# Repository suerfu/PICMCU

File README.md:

# PIC16F1788
Compilation of various code used to program PIC16F1788

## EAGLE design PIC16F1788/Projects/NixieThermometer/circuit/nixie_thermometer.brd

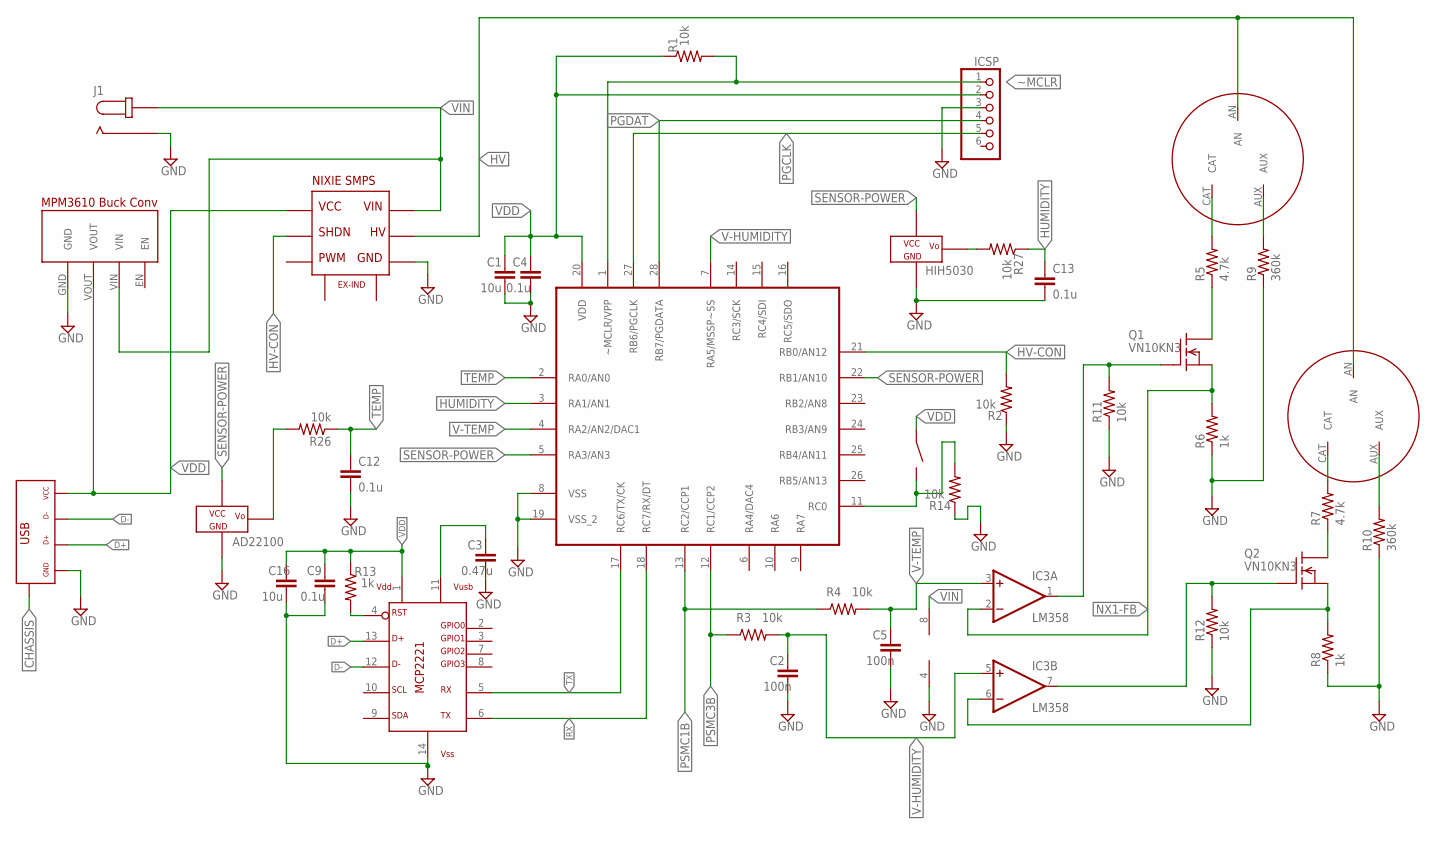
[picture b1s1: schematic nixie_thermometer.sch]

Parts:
AD22100: AD22100; TO-92
C1, C16: 10u; C0805
C2, C5: 100n; C0805
C3: 0.47u; C0805
C4, C9: 0.1u; C0805
C12, C13: 0.1u; C1206
HIH5030: HIH5030
IC1: PIC16F1788; DIP-28
IC2: MCP2221; SOIC-14
IC3: LM358; DIP-8
ICSP: PINHD-1X6; 1X06
J1: CONN-DC-JACK-PANEL; DC-JACK
Q1, Q2: VN10KN3; TO-92
R1, R2, R3, R4, R14, R26, R27: 10k; R0805
R5, R7: 4.7k; R0204/7
R6, R8: 1k; R0204/7
R9, R10: 360k; R0204/7
R11, R12: 10k; R0204/7
R13: 1k; R0805
U$1: MPM3610-ADAFRUIT; MPM3610-ADAFRUIT-MODULE
U$2: SMPS-HV-MODULE; SMPS-HV-MOD-MODULE
U$3, U$4: IN-13
U$5: SW-SPST-PUSHBUTTONSMD; SW-SPST-PUSHBUTTON-UNKNOWN-SMD
USB$2: USB-MILLMAX-896-43-004; USB-MILLMAX-896-43-004-90

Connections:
CHASSIS: USB$2.P$5 (SHIELD), USB$2.P$6 (SHIELD)
D+: IC2.13 (DP), USB$2.D+
D-: IC2.12 (DM), USB$2.D-
GND: AD22100.3 (GND), C1.2, C2.2, C3.2, C4.2, C5.2, C9.2, C12.2, C13.2, C16.2, HIH5030.GND, IC1.8 (VSS), IC1.19 (VSS_2), IC2.14 (VSS), IC3.4 (V-), ICSP.3, J1.GND-BOT (GND), J1.GND-TOP (GND), R2.1, R6.1, R8.1, R9.1, R10.1, R11.1, R12.1, R14.1, U$1.GND, U$2.GND, U$2.GND-HV (GND), USB$2.GND
HUMID-RAW: HIH5030.VO, R27.2
HUMIDITY: C13.1, IC1.3 (RA1/AN1), R27.1
HV: U$2.HV, U$3.AN, U$4.AN
HV-CON: IC1.21 (RB0/AN12), R2.2, U$2.SHDN
unnamed: IC1.11 (RC0), R14.2, U$5.P$6, U$5.P$8
unnamed: Q1.3 (D), R5.1
unnamed: Q2.3 (D), R7.1
unnamed: C3.1, IC2.11 (VUSB)
unnamed: R9.2, U$3.AUX
unnamed: R10.2, U$4.AUX
unnamed: R5.2, U$3.CAT
unnamed: R7.2, U$4.CAT
unnamed: IC2.4 (RST), R13.2
NX1-DRIVE: IC3.1 (OUT), Q1.2 (G), R11.2
NX1-FB: IC3.2 (-IN), Q1.1 (S), R6.2
NX2-DRIVE: IC3.7 (OUT), Q2.2 (G), R12.2
NX2-FB: IC3.6 (-IN), Q2.1 (S), R8.2
PGCLK: IC1.27 (RB6/PGCLK), ICSP.5
PGDAT: IC1.28 (RB7/PGDATA), ICSP.4
PSMC1B: IC1.13 (RC2/CCP1), R4.1
PSMC3B: IC1.12 (RC1/CCP2), R3.1
RX: IC1.18 (RC7/RX/DT), IC2.6 (TX)
SENSOR-POWER: AD22100.1 (VCC), HIH5030.VCC, IC1.5 (RA3/AN3), IC1.22 (RB1/AN10)
TEMP: C12.1, IC1.2 (RA0/AN0), R26.1
TEMP-RAW: AD22100.2 (VO), R26.2
TX: IC1.17 (RC6/TX/CK), IC2.5 (RX)
V-HUMIDITY: C2.1, IC1.7 (RA5/MSSP~SS), IC3.5 (+IN), R3.2
V-TEMP: C5.1, IC1.4 (RA2/AN2/DAC1), IC3.3 (+IN), R4.2
VDD: C1.1, C4.1, C9.1, C16.1, IC1.20 (VDD), IC2.1 (VDD), ICSP.2, R1.1, R13.1, U$1.VOUT, U$2.VDD (VCC), U$5.P$5, U$5.P$7, USB$2.VCC
VIN: IC3.8 (V+), J1.POW-BOT (POW), J1.POW-TOP (POW), U$1.VIN, U$2.VIN
~MCLR: IC1.1 (~MCLR/VPP), ICSP.1, R1.2

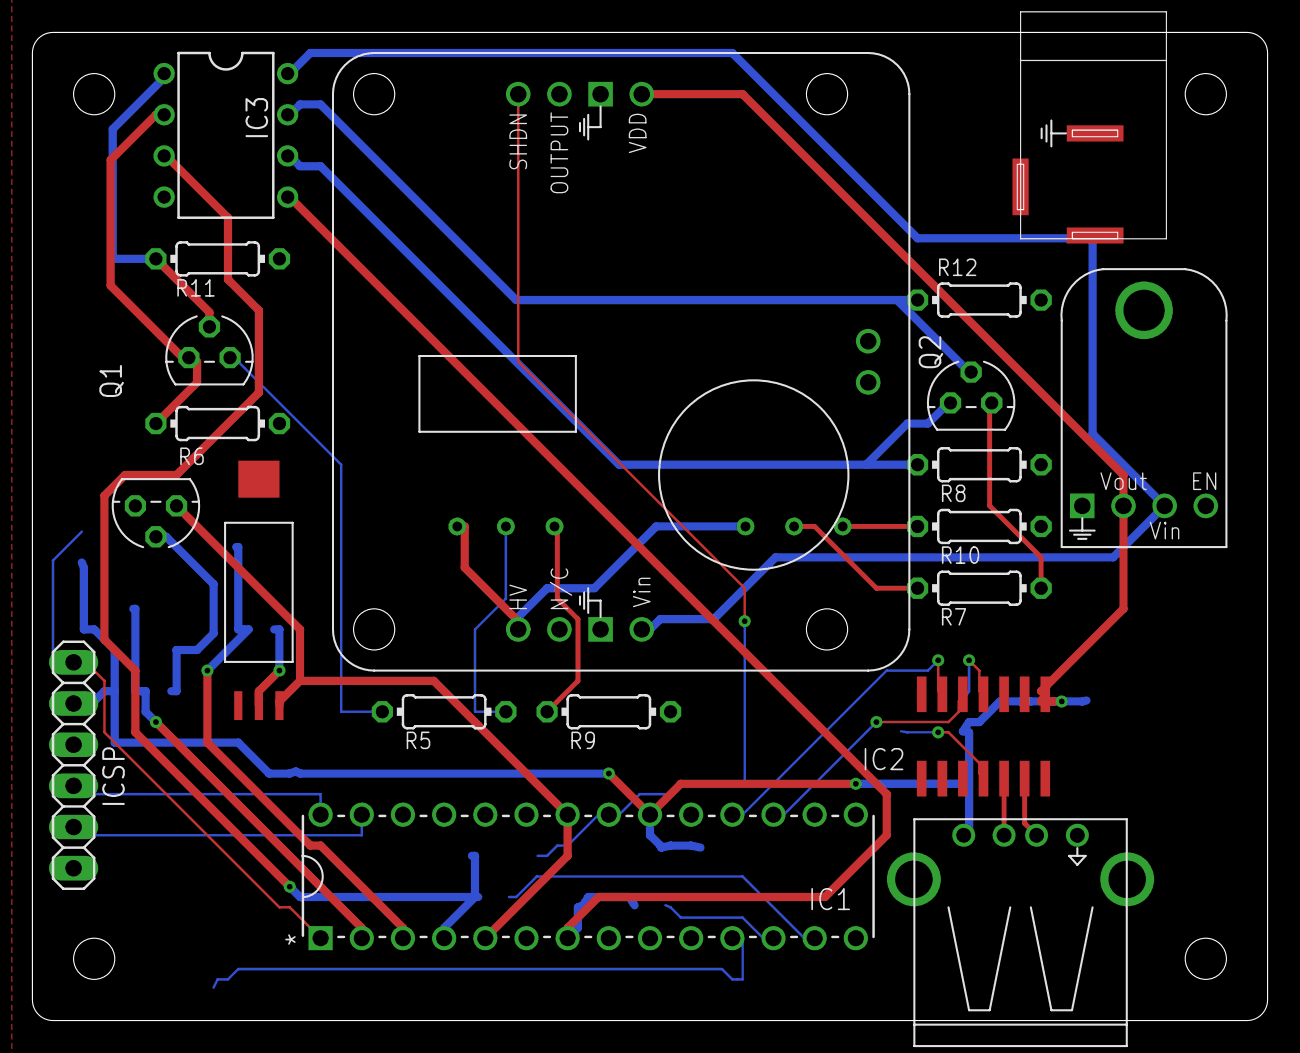
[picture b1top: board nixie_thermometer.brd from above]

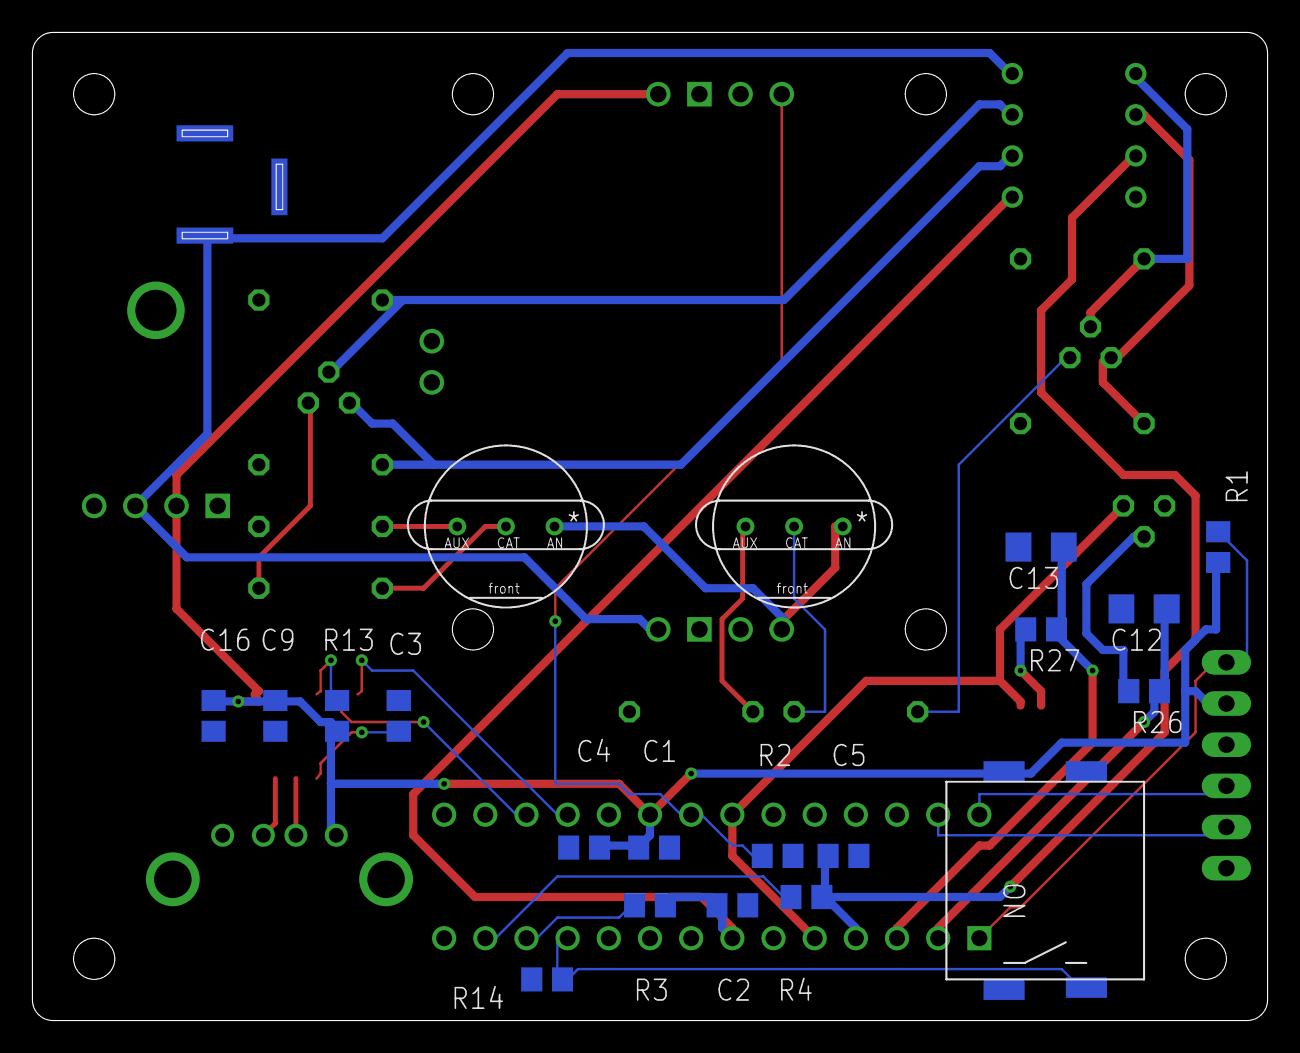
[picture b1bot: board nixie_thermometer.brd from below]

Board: 2 copper layers, 76.2 x 61.0 mm, 40 parts (20 on the bottom side), 35 nets.

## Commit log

2021-12-09 Create functions.h
    Added some commonly used function snippets.
2021-12-09 Added code used on general digital IO project.
2021-12-09 Added ADC related functions in functions.h
2021-12-09 Added some usage for DAC
2021-12-09 Fixed missing negative reference.
2021-12-09 ADRESL was shifting to the wrong direction.
2022-07-27 Restructured directories.
2022-07-27 Renamed General IO
2022-07-27 Added more documentation on clock oscillator
2022-07-27 Added PWM function through CCP module.
2022-07-27 Added PSMC function
2022-07-27 Added a shorter SetPSMC1 function in addition.
2022-08-09 Added PWM project folder.
2022-08-09 PWM with duty cycle changing over time
2022-08-09 Added contents in PWM/functions.h
2022-08-10 PWM period configurable via commandline UART
2022-08-15 added details on UART
2022-08-15 Setting port c value for UART RX and TX pins
    Needed so that MCP2221A can pull RX pin of MCU high. This could be a hardware bug in PIC MCU.
2022-08-17 Changed ADC clock to Fosc/32, and added ADFVR
2022-08-17 RX of UART was not working because TRISC was set to 0 by PSMC.
2022-08-17 improved ADC module by adding integer readout and default pos and neg channels.
2022-08-17 Corrected and added more documentation in PSMC
2022-08-17 Added files for the USB Geiger counter project.
2022-08-17 Using twobytes and union to set period and duty cycle.
2022-08-20 Code working for the Geiger counter.
2022-08-24 Added TMR1 functions.
2022-08-24 Added CCP configuration function
2022-08-24 Added interrupt-related functions
2022-08-24 Geiger counter functional. Added notebooks to plot the data. Added CAD file for counter's bottom cover
2022-08-25 Added functions to control LCD display. LCD clears and blinks.
2022-08-25 LCD cursor positioning working.
2022-08-26 Working Geiger counter project.
2022-08-26 added EEPROM operations in the overall functions.
2022-08-30 Added enclosure design files for the USB Geiger counter project and started the Nixie clock project.
2022-09-03 Added functions to read ambient light intensity. Temporarily disabled LCD screen printing.
2022-09-03 Forgot to disable the printing of CPM rate each minute.
2022-09-07 Configured and took phototransistor data.
2022-09-07 Added feature to control brightness of the LCD screen, but CCP1 PWM and timer/counter is conflicting with each other.
2022-09-08 Using CCP2 to count time; CCP1 is used to drive LCD brightness via PWM. Brightness adjustment working.
2022-09-08 LCD and brightness adjustment working. Earlier not seeing characters because the contrast was not high enough. To-do: auto-adjust brightness.
2022-09-08 Brightness auto-adjustment working.
2022-09-08 UART sending HV and brightness information as well. Moved UART send from interrupt to main.
2022-09-08 Moved LCD adjustment function to interrupt hander for smooth adjustment.
2022-09-10 Added function to provide default PR and DC values, as the chip default value would turn the transistor always on and drain too much power.
2022-10-24 Modified Geiger counter cover for manufacturing.
2022-10-25 USART working, but Charlieplexing not completely functional due to serial LED of different colors.
2022-10-25 ADC functions verified except PM2.5 and VOC. Also added interrupt handler, CCP2 and Timer1
2022-10-27 Added TMR0 functions and using TMR0 and interrupt to get VOC reading. Functional.
2022-12-28 ADC and UART working.
2022-12-28 Added EAGLE PCB files
2022-12-28 Added CAD file for enclosure.
2022-12-28 Fixed the bug of default value of HV being high.
2022-12-29 Added PSMC in main code. Not verified yet.
2022-12-30 Nixie display working. Column rises slowly and continuously.
2022-12-30 Interrupt on change and sleep mode working; reorganized code in a better format.
2024-10-14 added comments to functions.h
2024-10-14 added prelim code for dealing with I2C write. Not tested nor compiled.
2024-10-14 I2C function in progress; UART is working over BT.
2024-10-15 put mssp in a separate file; i2c working.
2024-10-15 added comments about essential functions in I2C; reorganized directory structure in main.
2024-10-15 in main, renamed functions -> lib; also created separate file for uart.
2024-10-15 added functioning i2c/mssp header to nixieclock
2024-10-15 LED control sort of working: address + >> operation can change the 0xC part of the fixed address, so use bitwise operation instead!
2024-10-15 prelim version of config led working inside main function.
2024-10-15 config_led working under a function
2024-10-15 bug: once read is attempted, the device will fail since then on, it is likely it is related to the memory of the led driver
2024-10-16 I2C read function is also working; put code together into a single function that does read and write sequences.
2024-10-16 RGB led working in the random mode.
2024-10-16 Using a MAX_PWM to control brightness consistently.
2025-01-04 added watchdog timer function to Nixie thermometer
2025-08-02 reorganized the directory
2025-08-02 removed lib directory
2025-08-04 created clock and port as separate header files separate from functions.h
